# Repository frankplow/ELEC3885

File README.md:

# A robust and lightweight helmet-mounted safety camera for cycling
ELEC3885: Group Design Project, group 4 project at the University of Leeds.

The objective of this project is to design and produce a prototype for a camera to mount to the helmet of a cyclist, as well as a software suite for the analysis of footage and user documentation. The camera is intended as a safety device, for example for use in legal proceedings, rather than an 'action cam'. Because of this, it should be low-cost and should not require much effort by the user, for example charging, to use.

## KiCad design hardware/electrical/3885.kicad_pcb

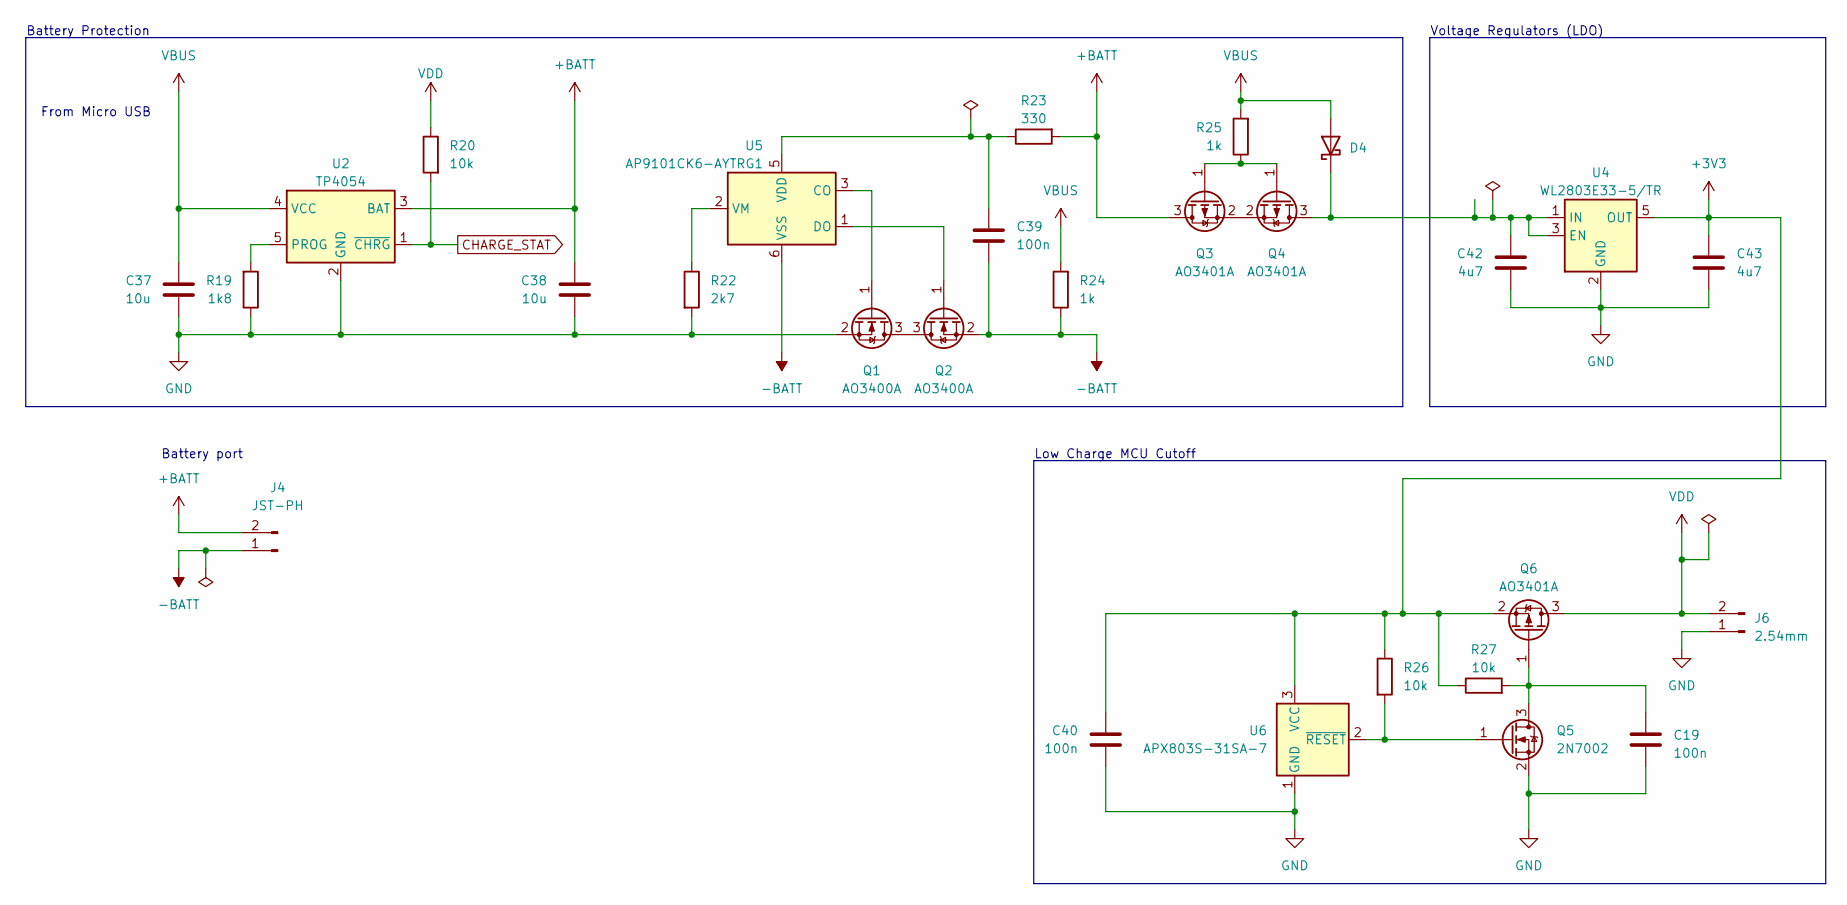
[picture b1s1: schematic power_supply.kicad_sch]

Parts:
C19, C39, C40: 100n; C_0402_1005Metric; Mfr. Part # CL05B104KO5NNNC; LCSC Part # C1525
C37, C38: 10u; C_0402_1005Metric; Mfr. Part # CL05A106MQ5NUNC; LCSC Part # C15525
C42, C43: 4u7; C_0402_1005Metric; Mfr. Part # CL05A475MP5NRNC; LCSC Part # C23733
D4: D_Schottky; D_SOD-323; Mfr. Part # 1N5819WS; LCSC Part # C191023
J4: JST-PH; JST_PH_S2B-PH-K_1x02_P2.00mm_Horizontal; Mfr. Part # S2B-PH-K-S(LF)(SN); LCSC Part # C173752
J6: 2.54mm; PinHeader_1x02_P2.54mm_Vertical
Q1, Q2: AO3400A; SOT-23; Mfr. Part # AO3400A; LCSC Part # C20917
Q3, Q4, Q6: AO3401A; SOT-23; Mfr. Part # AO3401A; LCSC Part # C15127
Q5: 2N7002; SOT-23; Mfr. Part # 2N7002; LCSC Part # C8545
R19: 1k8; R_0603_1608Metric; Mfr. Part # 0603WAF1801T5E; LCSC Part # C4177
R20, R26, R27: 10k; R_0402_1005Metric; Mfr. Part # 0402WGF1002TCE; LCSC Part # C25744
R22: 2k7; R_0603_1608Metric; Mfr. Part # 0603WAF2701T5E; LCSC Part # C13167
R23: 330; R_0402_1005Metric; Mfr. Part # 0402WGF3300TCE; LCSC Part # C25104
R24, R25: 1k; R_0402_1005Metric; Mfr. Part # 0402WGF1001TCE; LCSC Part # C11702
U2: TP4054; SOT-23-5; Mfr. Part # TP4054-42-SOT25R; LCSC Part # C32574
U4: WL2803E33-5/TR; SOT-23-5; Mfr. Part # WL2803E33-5/TR; LCSC Part # C192928
U5: AP9101CK6-AYTRG1; SOT-23-6; Mfr. Part # AP9101CK6-AYTRG1; LCSC Part # C507889
U6: APX803S-31SA-7; SOT-23; Mfr. Part # APX803S-31SA-7; LCSC Part # C129757

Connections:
+3V3: C40.1, C43.2, Q6.2 (S), R26.1, R27.1, U4.5 (OUT), U6.3 (VCC); also elsewhere on the board
+BATT: C38.2, J4.2, Q3.3 (D), R23.2, U2.3 (BAT)
-BATT: C39.1, J4.1, Q2.2 (S), R24.1, U5.6 (VSS)
CHARGE_STAT: R20.2, U2.1 (~CHRG); also elsewhere on the board
GND: C19.2, C37.2, C38.1, C40.2, C42.1, C43.1, J6.1, Q1.2 (S), Q5.2 (S), R19.1, R22.2, U2.2 (GND), U4.2 (GND), U6.1 (GND); also elsewhere on the board
unnamed: C42.2, D4.1 (K), Q4.3 (D), U4.1 (IN), U4.3 (EN)
unnamed: Q1.3 (D), Q2.3 (D)
unnamed: Q1.1 (G), U5.3 (CO)
unnamed: Q2.1 (G), U5.1 (DO)
unnamed: Q3.1 (G), Q4.1 (G), R25.1
unnamed: Q3.2 (S), Q4.2 (S)
unnamed: C19.1, Q5.3 (D), Q6.1 (G), R27.2
unnamed: Q5.1 (G), R26.2, U6.2 (~RESET)
unnamed: R19.2, U2.5 (PROG)
unnamed: C39.2, R23.1, U5.5 (VDD)
unnamed: R22.1, U5.2 (VM)
VBUS: C37.1, D4.2 (A), R24.2, R25.2, U2.4 (VCC); also elsewhere on the board
VDD: J6.2, Q6.3 (D), R20.1; also elsewhere on the board

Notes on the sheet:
Voltage Regulators (LDO)
Low Charge MCU Cutoff
From Micro USB
Battery Protection
Battery port

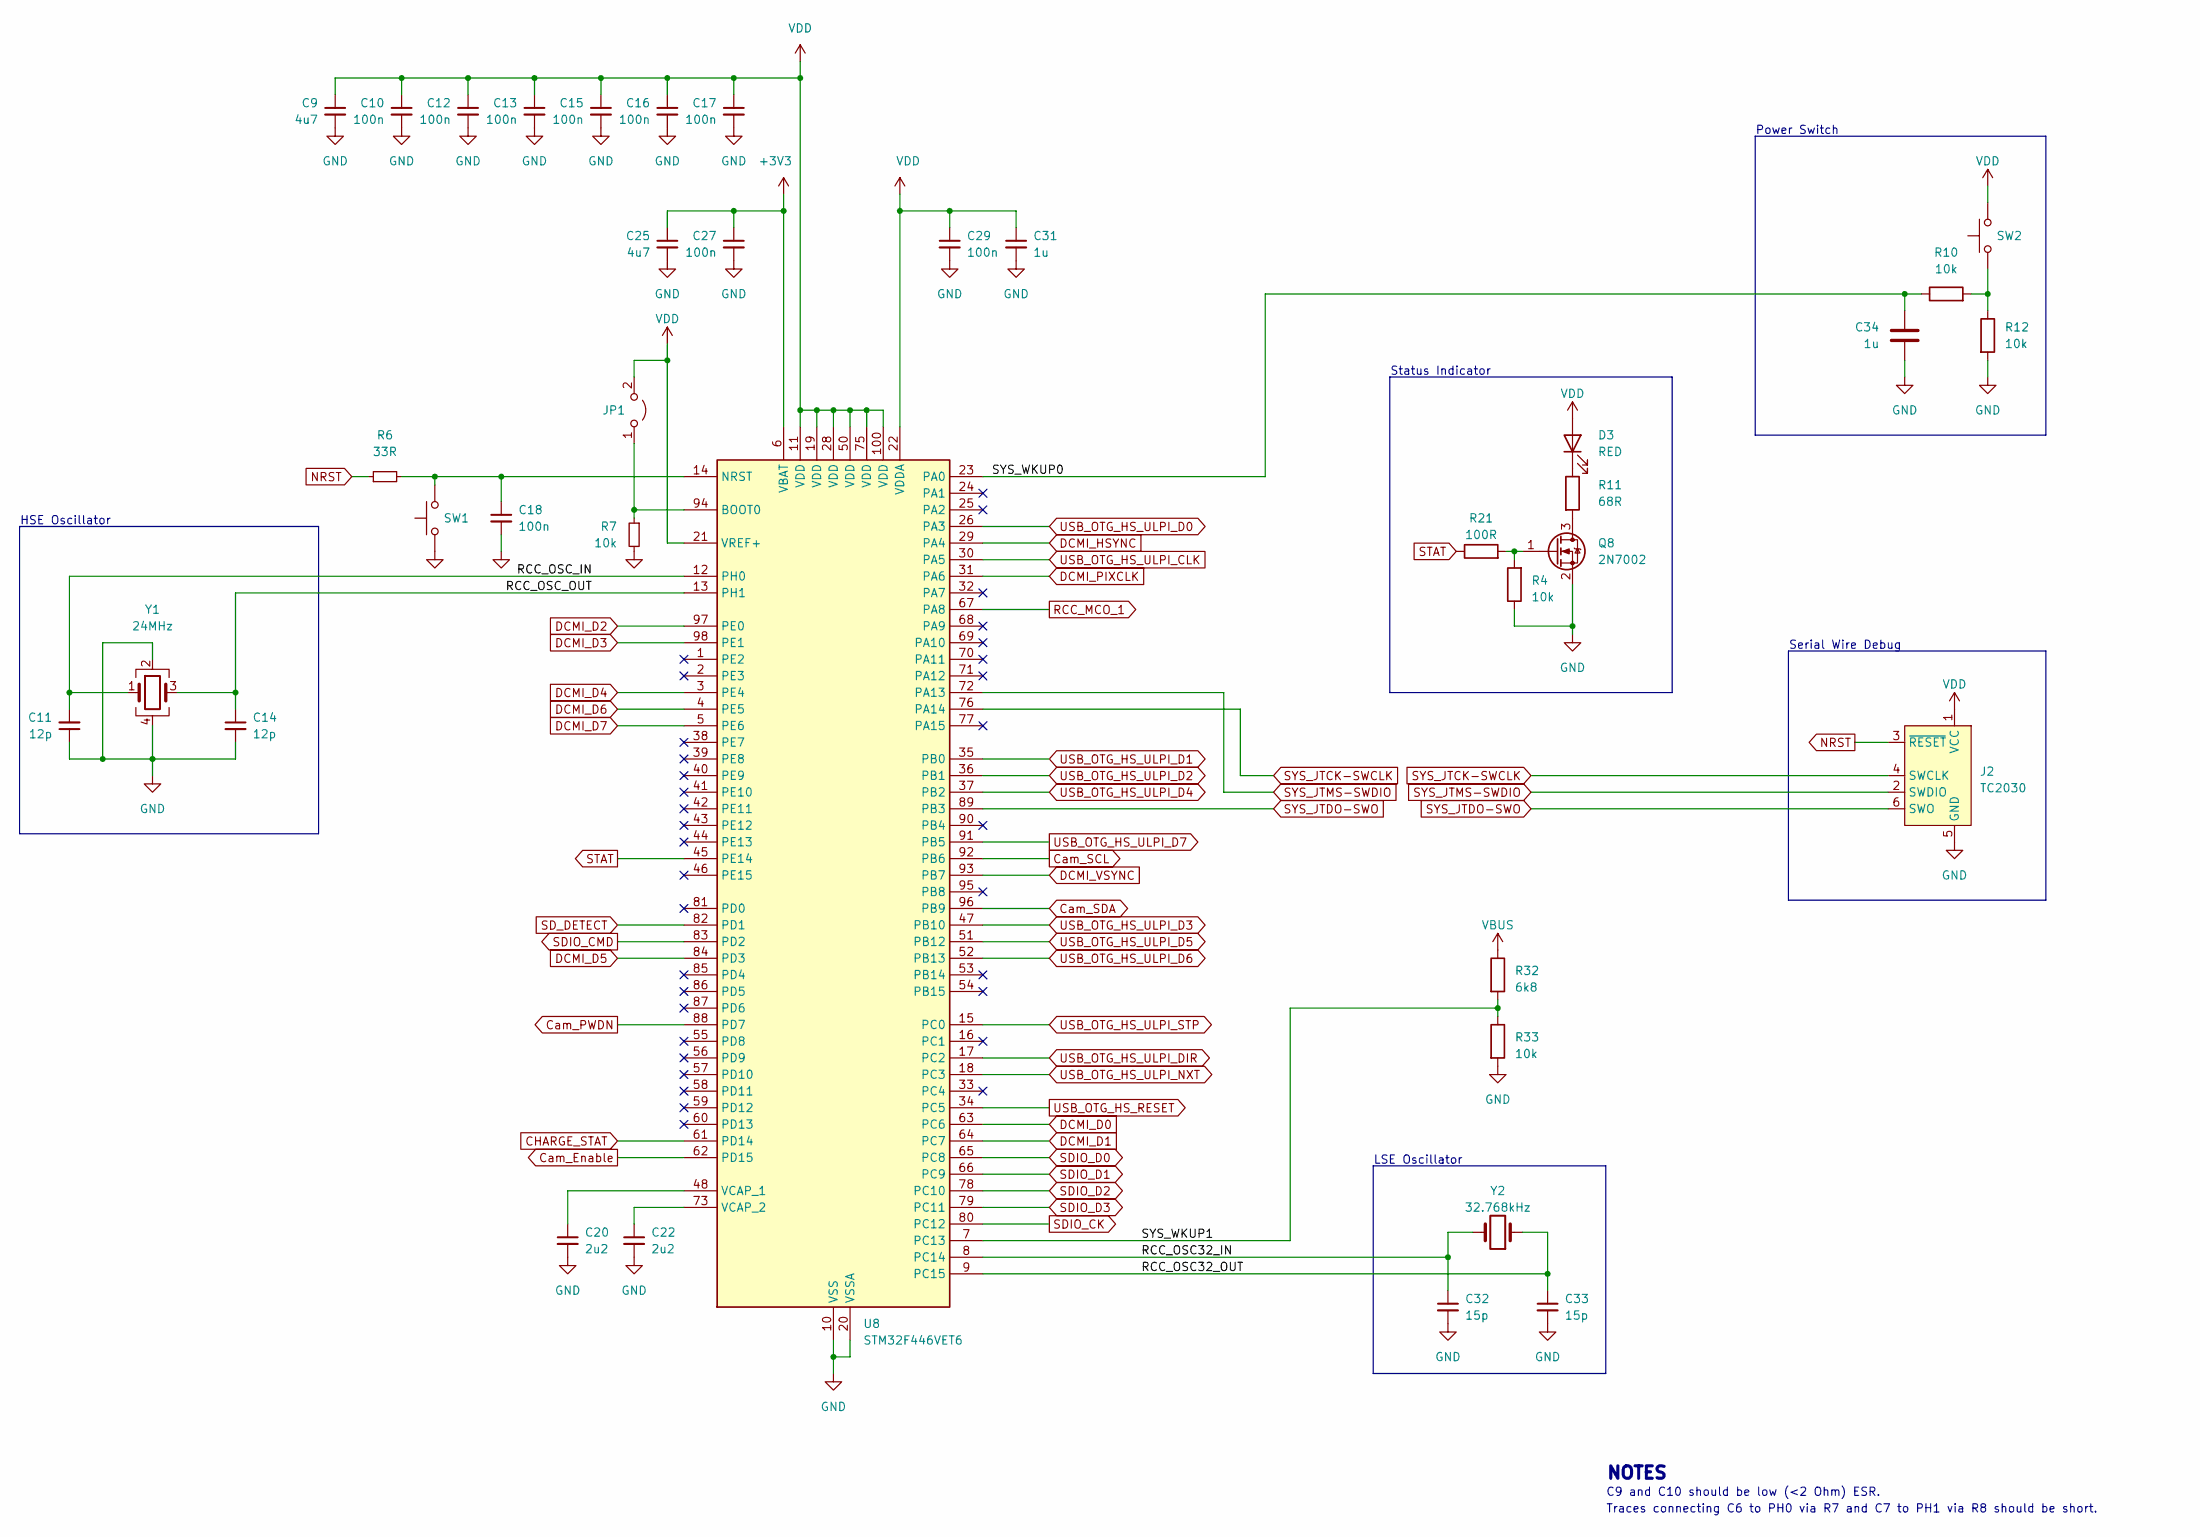
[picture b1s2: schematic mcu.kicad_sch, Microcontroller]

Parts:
C9, C25: 4u7; C_0402_1005Metric; Mfr. Part # CL05A475MP5NRNC; LCSC Part # C23733
C10, C12, C13, C15, C16, C17, C18, C27, C29: 100n; C_0402_1005Metric; Mfr. Part # CL05B104KO5NNNC; LCSC Part # C1525
C11, C14: 12p; C_0603_1608Metric; Mfr. Part # CL10C120JB8NNNC; LCSC Part # C38523
C20, C22: 2u2; C_0402_1005Metric; Mfr. Part # CL05A225MQ5NSNC; LCSC Part # C12530
C31, C34: 1u; C_0402_1005Metric; Mfr. Part # CL05A105KA5NQNC; LCSC Part # C52923
C32, C33: 15p; C_0603_1608Metric; Mfr. Part # CL10C150JB8NNNC; LCSC Part # C1644
D3: RED; Everlight_21-21S; Mfr. Part # 12-21SURC/S530-A3/TR8; LCSC Part # C131288
J2: TC2030; Tag-Connect_TC2030-IDC-FP_2x03_P1.27mm_Vertical
JP1: Jumper_2_Open; SolderJumper-2_P1.3mm_Open_Pad1.0x1.5mm
Q8: 2N7002; SOT-23; Mfr. Part # 2N7002; LCSC Part # C8545
R4: 10k; R_0402_1005Metric; Mfr. Part # 0402WGF1000TCE; LCSC Part # C25076
R6: 33R; R_0402_1005Metric; Mfr. Part # 0402WGF330JTCE; LCSC Part # C25105
R7, R10, R12, R33: 10k; R_0402_1005Metric; Mfr. Part # 0402WGF1002TCE; LCSC Part # C25744
R11: 68R; R_0603_1608Metric; Mfr. Part # 0603WAF680JT5E; LCSC Part # C27592
R21: 100R; R_0402_1005Metric; Mfr. Part # 0402WGF1000TCE; LCSC Part # C25076
R32: 6k8; R_0402_1005Metric; Mfr. Part # 0402WGF6801TCE; LCSC Part # C25917
SW1: TS-1187A-B-A-B; SW_SPST_XKB_TS-1187A; Mfr. Part # TS-1187A-B-A-B; LCSC Part # C318884
SW2: GT-TC018B-H0375-L1; G-Switch_GT-TC018; Mfr. Part # GT-TC018B-H0375-L1; LCSC Part # C2762970
U8: STM32F446VET6; LQFP-100_14x14mm_P0.5mm; Mfr. Part # STM32F446VET6; LCSC Part # C91929
Y1: 24MHz; Crystal_SMD_SeikoEpson_TSX3225-4Pin_3.2x2.5mm; Mfr. Part # X1E0000210129; LCSC Part # C255917
Y2: 32.768kHz; Crystal_SMD_3215-2Pin_3.2x1.5mm; Mfr. Part # Q13FC1350000400; LCSC Part # C32346

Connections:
+3V3: C25.1, C27.1, U8.6 (VBAT); also elsewhere on the board
/Microcontroller/RCC_OSC32_IN: C32.1, U8.8 (PC14), Y2.2
/Microcontroller/RCC_OSC32_OUT: C33.1, U8.9 (PC15), Y2.1
/Microcontroller/RCC_OSC_IN: C11.2, U8.12 (PH0), Y1.1
/Microcontroller/RCC_OSC_OUT: C14.1, U8.13 (PH1), Y1.3
/Microcontroller/SYS_WKUP0: C34.2, R10.1, U8.23 (PA0)
/Microcontroller/SYS_WKUP1: R32.2, R33.1, U8.7 (PC13)
CHARGE_STAT: U8.61 (PD14); also elsewhere on the board
Cam_Enable: U8.62 (PD15); also elsewhere on the board
Cam_PWDN: U8.88 (PD7); also elsewhere on the board
Cam_SCL: U8.92 (PB6); also elsewhere on the board
Cam_SDA: U8.96 (PB9); also elsewhere on the board
DCMI_D0: U8.63 (PC6); also elsewhere on the board
DCMI_D1: U8.64 (PC7); also elsewhere on the board
DCMI_D2: U8.97 (PE0); also elsewhere on the board
DCMI_D3: U8.98 (PE1); also elsewhere on the board
DCMI_D4: U8.3 (PE4); also elsewhere on the board
DCMI_D5: U8.84 (PD3); also elsewhere on the board
DCMI_D6: U8.4 (PE5); also elsewhere on the board
DCMI_D7: U8.5 (PE6); also elsewhere on the board
DCMI_HSYNC: U8.29 (PA4); also elsewhere on the board
DCMI_PIXCLK: U8.31 (PA6); also elsewhere on the board
DCMI_VSYNC: U8.93 (PB7); also elsewhere on the board
GND: C9.2, C10.2, C11.1, C12.2, C13.2, C14.2, C15.2, C16.2, C17.2, C18.2, C20.2, C22.2, C25.2, C27.2, C29.2, C31.2, C32.2, C33.2, C34.1, J2.5 (GND), Q8.2 (S), R4.1, R7.2, R12.2, R33.2, SW1.1, U8.10 (VSS), U8.20 (VSSA), U8.27 (VSS), U8.49 (VSS), U8.74 (VSS), U8.99 (VSS), Y1.2, Y1.4; also elsewhere on the board
NRST: J2.3 (~RESET), R6.1
unnamed: D3.1 (K), R11.1
unnamed: JP1.1 (A), R7.1, U8.94 (BOOT0)
unnamed: Q8.3 (D), R11.2
unnamed: Q8.1 (G), R4.2, R21.2
unnamed: R10.2, R12.1, SW2.1
unnamed: C18.1, R6.2, SW1.2, U8.14 (NRST)
unnamed: C20.1, U8.48 (VCAP_1)
unnamed: C22.1, U8.73 (VCAP_2)
RCC_MCO_1: U8.67 (PA8); also elsewhere on the board
SDIO_CK: U8.80 (PC12); also elsewhere on the board
SDIO_CMD: U8.83 (PD2); also elsewhere on the board
SDIO_D0: U8.65 (PC8); also elsewhere on the board
SDIO_D1: U8.66 (PC9); also elsewhere on the board
SDIO_D2: U8.78 (PC10); also elsewhere on the board
SDIO_D3: U8.79 (PC11); also elsewhere on the board
SD_DETECT: U8.82 (PD1); also elsewhere on the board
STAT: R21.1, U8.45 (PE14)
SYS_JTCK-SWCLK: J2.4 (SWCLK), U8.76 (PA14)
SYS_JTDO-SWO: J2.6 (SWO), U8.89 (PB3)
SYS_JTMS-SWDIO: J2.2 (SWDIO), U8.72 (PA13)
USB_OTG_HS_RESET: U8.34 (PC5); also elsewhere on the board
USB_OTG_HS_ULPI_CLK: U8.30 (PA5); also elsewhere on the board
USB_OTG_HS_ULPI_D0: U8.26 (PA3); also elsewhere on the board
USB_OTG_HS_ULPI_D1: U8.35 (PB0); also elsewhere on the board
USB_OTG_HS_ULPI_D2: U8.36 (PB1); also elsewhere on the board
USB_OTG_HS_ULPI_D3: U8.47 (PB10); also elsewhere on the board
USB_OTG_HS_ULPI_D4: U8.37 (PB2); also elsewhere on the board
USB_OTG_HS_ULPI_D5: U8.51 (PB12); also elsewhere on the board
USB_OTG_HS_ULPI_D6: U8.52 (PB13); also elsewhere on the board
USB_OTG_HS_ULPI_D7: U8.91 (PB5); also elsewhere on the board
USB_OTG_HS_ULPI_DIR: U8.17 (PC2); also elsewhere on the board
USB_OTG_HS_ULPI_NXT: U8.18 (PC3); also elsewhere on the board
USB_OTG_HS_ULPI_STP: U8.15 (PC0); also elsewhere on the board
VBUS: R32.1; also elsewhere on the board
VDD: C9.1, C10.1, C12.1, C13.1, C15.1, C16.1, C17.1, C29.1, C31.1, D3.2 (A), J2.1 (VCC), JP1.2 (B), SW2.2, U8.11 (VDD), U8.19 (VDD), U8.21 (VREF+), U8.22 (VDDA), U8.28 (VDD), U8.50 (VDD), U8.75 (VDD), U8.100 (VDD); also elsewhere on the board

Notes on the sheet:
C9 and C10 should be low (<2 Ohm) ESR.
Traces connecting C6 to PH0 via R7 and C7 to PH1 via R8 should be short.
LSE Oscillator
Serial Wire Debug
HSE Oscillator
Status Indicator
NOTES
Power Switch

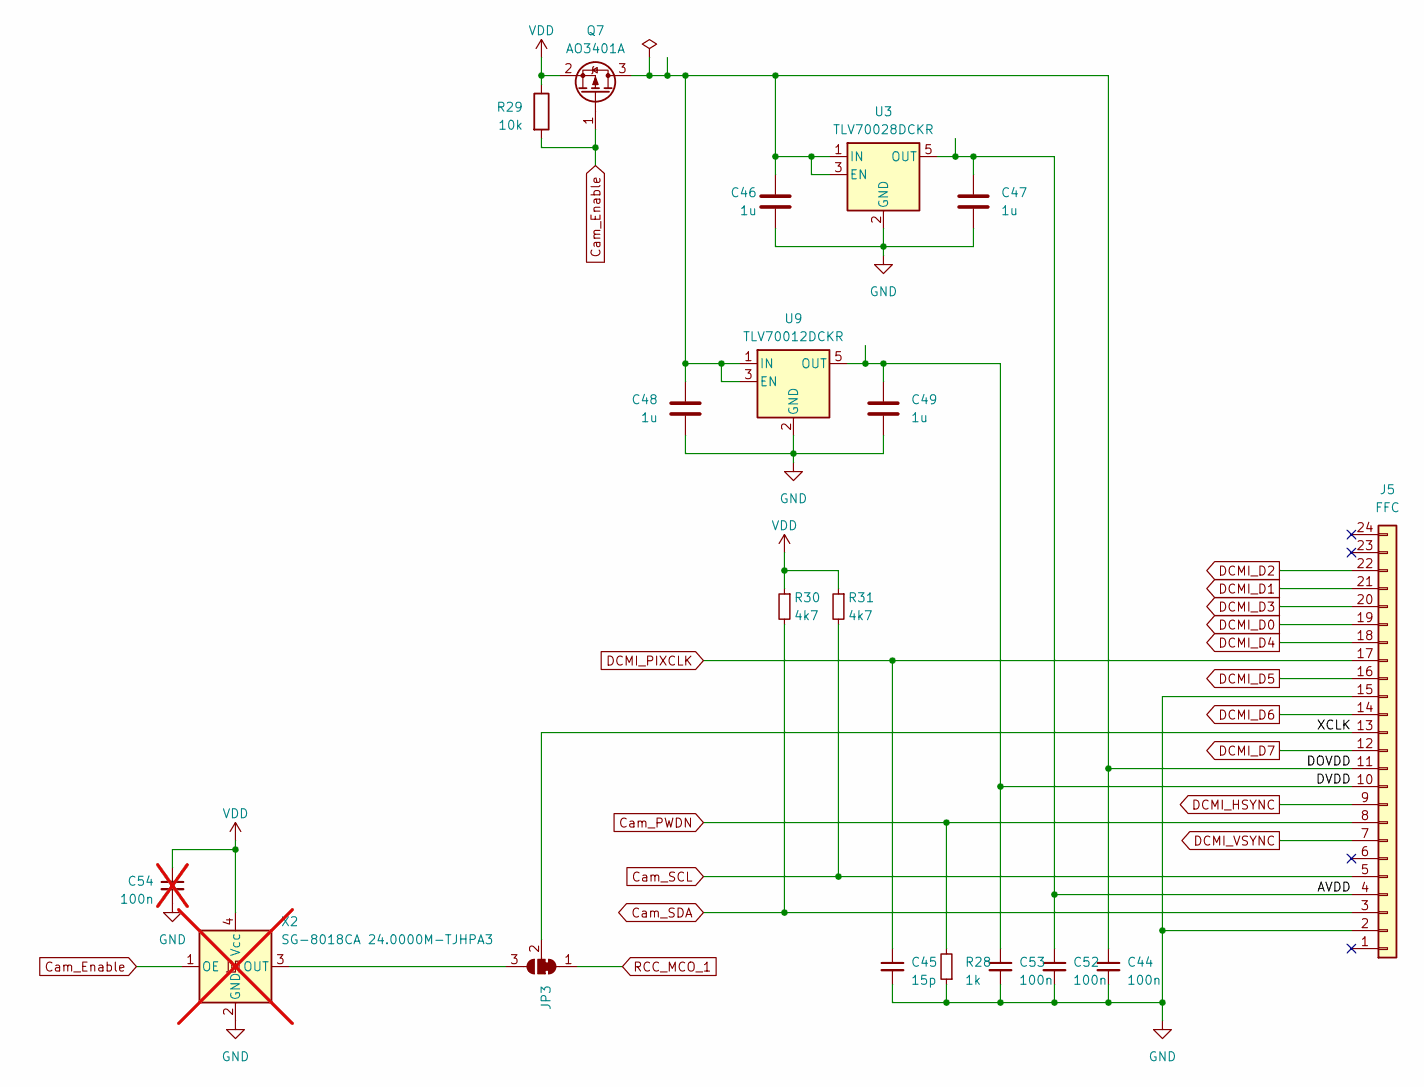
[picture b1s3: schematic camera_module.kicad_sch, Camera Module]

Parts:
C44, C52, C53: 100n; C_0402_1005Metric; Mfr. Part # CL05B104KO5NNNC; LCSC Part # C1525
C45: 15p; C_0603_1608Metric; Mfr. Part # CL10C150JB8NNNC; LCSC Part # C1644
C46, C47, C48, C49: 1u; C_0402_1005Metric; Mfr. Part # CL05A105KA5NQNC; LCSC Part # C52923
C54: 100n; C_0402_1005Metric; Mfr. Part # CL05B104KO5NNNC; LCSC Part # C1525; not fitted
J5: FFC; Jushuo_AFC07-S24ECA-00_1x24-1MP_P0.50_Horizontal; Mfr. Part # AFC07-S24ECA-00; LCSC Part # C262643
JP3: SolderJumper_3_Bridged12; SolderJumper-3_P1.3mm_Bridged12_Pad1.0x1.5mm
Q7: AO3401A; SOT-23; Mfr. Part # AO3401A; LCSC Part # C15127
R28: 1k; R_0402_1005Metric; Mfr. Part # 0402WGF1001TCE; LCSC Part # C11702
R29: 10k; R_0402_1005Metric; Mfr. Part # 0402WGF1002TCE; LCSC Part # C25744
R30, R31: 4k7; R_0402_1005Metric; Mfr. Part # 0402WGF4701TCE; LCSC Part # C25900
U3: TLV70028DCKR; SOT-353_SC-70-5; Mfr. Part # TLV70028DCKR; LCSC Part # C398921
U9: TLV70012DCKR; SOT-353_SC-70-5; Mfr. Part # TLV70012DCKR; LCSC Part # C96219
X2: SG-8018CA 24.0000M-TJHPA3; Oscillator_SMD_SeikoEpson_SG8002CA-4Pin_7.0x5.0mm_HandSolde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; not fitted

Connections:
/Camera Module/AVDD: C47.1, C52.1, J5.4, U3.5 (OUT)
/Camera Module/DOVDD: C44.1, C46.1, C48.1, J5.11, Q7.3 (D), U3.1 (IN), U3.3 (EN), U9.1 (IN), U9.3 (EN)
/Camera Module/DVDD: C49.1, C53.1, J5.10, U9.5 (OUT)
/Camera Module/XCLK: J5.13, JP3.2 (C)
Cam_Enable: Q7.1 (G), R29.2, X2.1 (OE); also elsewhere on the board
Cam_PWDN: J5.8, R28.2; also elsewhere on the board
Cam_SCL: J5.5, R31.2; also elsewhere on the board
Cam_SDA: J5.3, R30.2; also elsewhere on the board
DCMI_D0: J5.19; also elsewhere on the board
DCMI_D1: J5.21; also elsewhere on the board
DCMI_D2: J5.22; also elsewhere on the board
DCMI_D3: J5.20; also elsewhere on the board
DCMI_D4: J5.18; also elsewhere on the board
DCMI_D5: J5.16; also elsewhere on the board
DCMI_D6: J5.14; also elsewhere on the board
DCMI_D7: J5.12; also elsewhere on the board
DCMI_HSYNC: J5.9; also elsewhere on the board
DCMI_PIXCLK: C45.1, J5.17; also elsewhere on the board
DCMI_VSYNC: J5.7; also elsewhere on the board
GND: C44.2, C45.2, C46.2, C47.2, C48.2, C49.2, C52.2, C53.2, C54.2, J5.2, J5.15, R28.1, U3.2 (GND), U9.2 (GND), X2.2 (GND); also elsewhere on the board
unnamed: JP3.3 (B), X2.3 (OUT)
RCC_MCO_1: JP3.1 (A); also elsewhere on the board
VDD: C54.1, Q7.2 (S), R29.1, R30.1, R31.1, X2.4 (Vcc); also elsewhere on the board

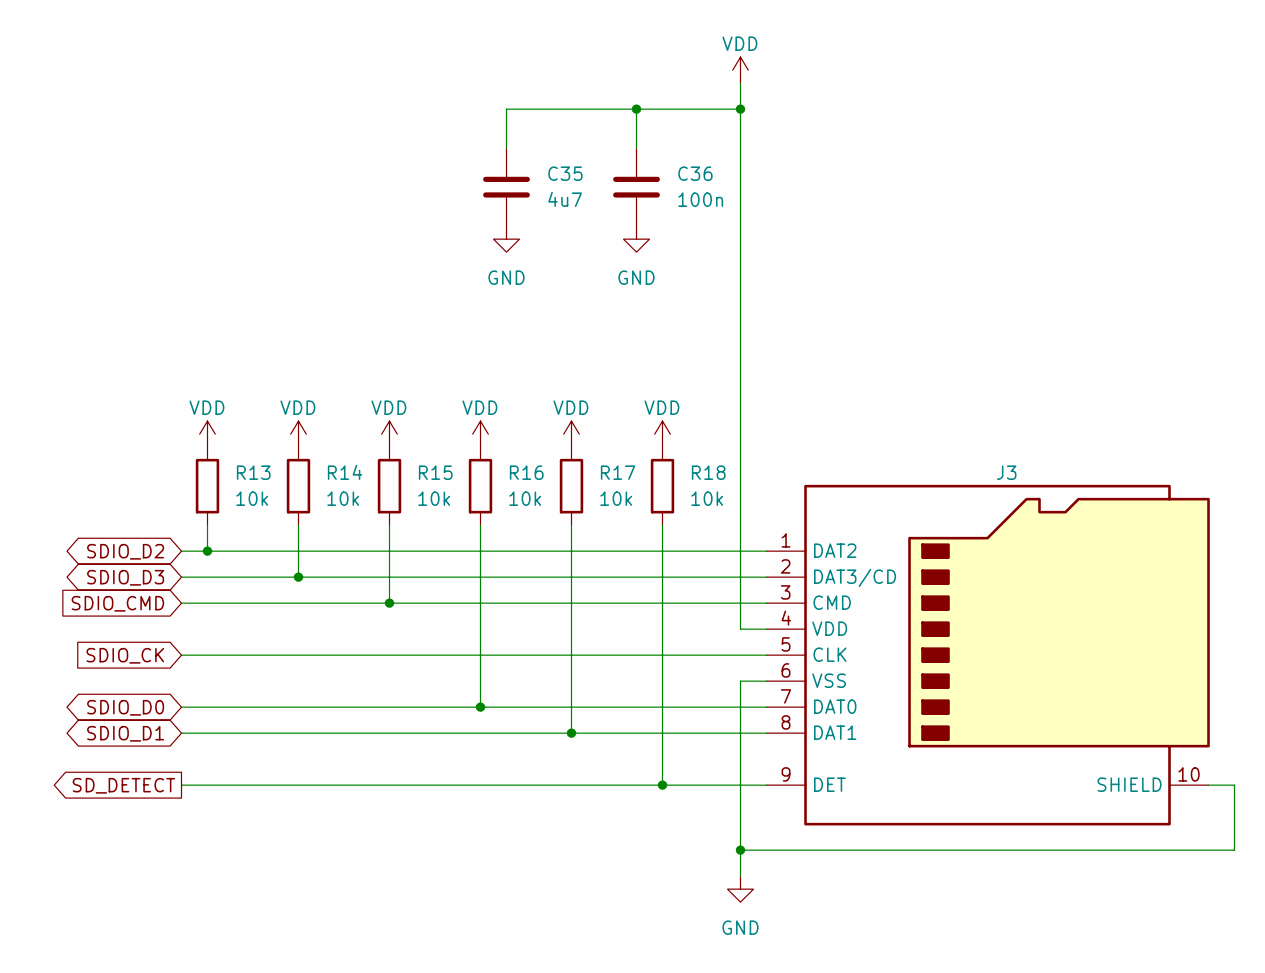
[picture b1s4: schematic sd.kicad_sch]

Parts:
C35: 4u7; C_0402_1005Metric; Mfr. Part # CL05A475MP5NRNC; LCSC Part # C23733
C36: 100n; C_0402_1005Metric; Mfr. Part # CL05B104KO5NNNC; LCSC Part # C1525
J3: Micro_SD_Card_Det1; microSD_HC_XKB_XKTF-N02-N; Mfr. Part # XKTF-N02-N; LCSC Part # C381084
R13, R14, R15, R16, R17, R18: 10k; R_0402_1005Metric; Mfr. Part # 0402WGF1002TCE; LCSC Part # C25744

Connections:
GND: C35.2, C36.2, J3.6 (VSS), J3.10 (SHIELD); also elsewhere on the board
SDIO_CK: J3.5 (CLK); also elsewhere on the board
SDIO_CMD: J3.3 (CMD), R15.2; also elsewhere on the board
SDIO_D0: J3.7 (DAT0), R16.2; also elsewhere on the board
SDIO_D1: J3.8 (DAT1), R17.2; also elsewhere on the board
SDIO_D2: J3.1 (DAT2), R13.2; also elsewhere on the board
SDIO_D3: J3.2 (DAT3/CD), R14.2; also elsewhere on the board
SD_DETECT: J3.9 (DET), R18.2; also elsewhere on the board
VDD: C35.1, C36.1, J3.4 (VDD), R13.1, R14.1, R15.1, R16.1, R17.1, R18.1; also elsewhere on the board

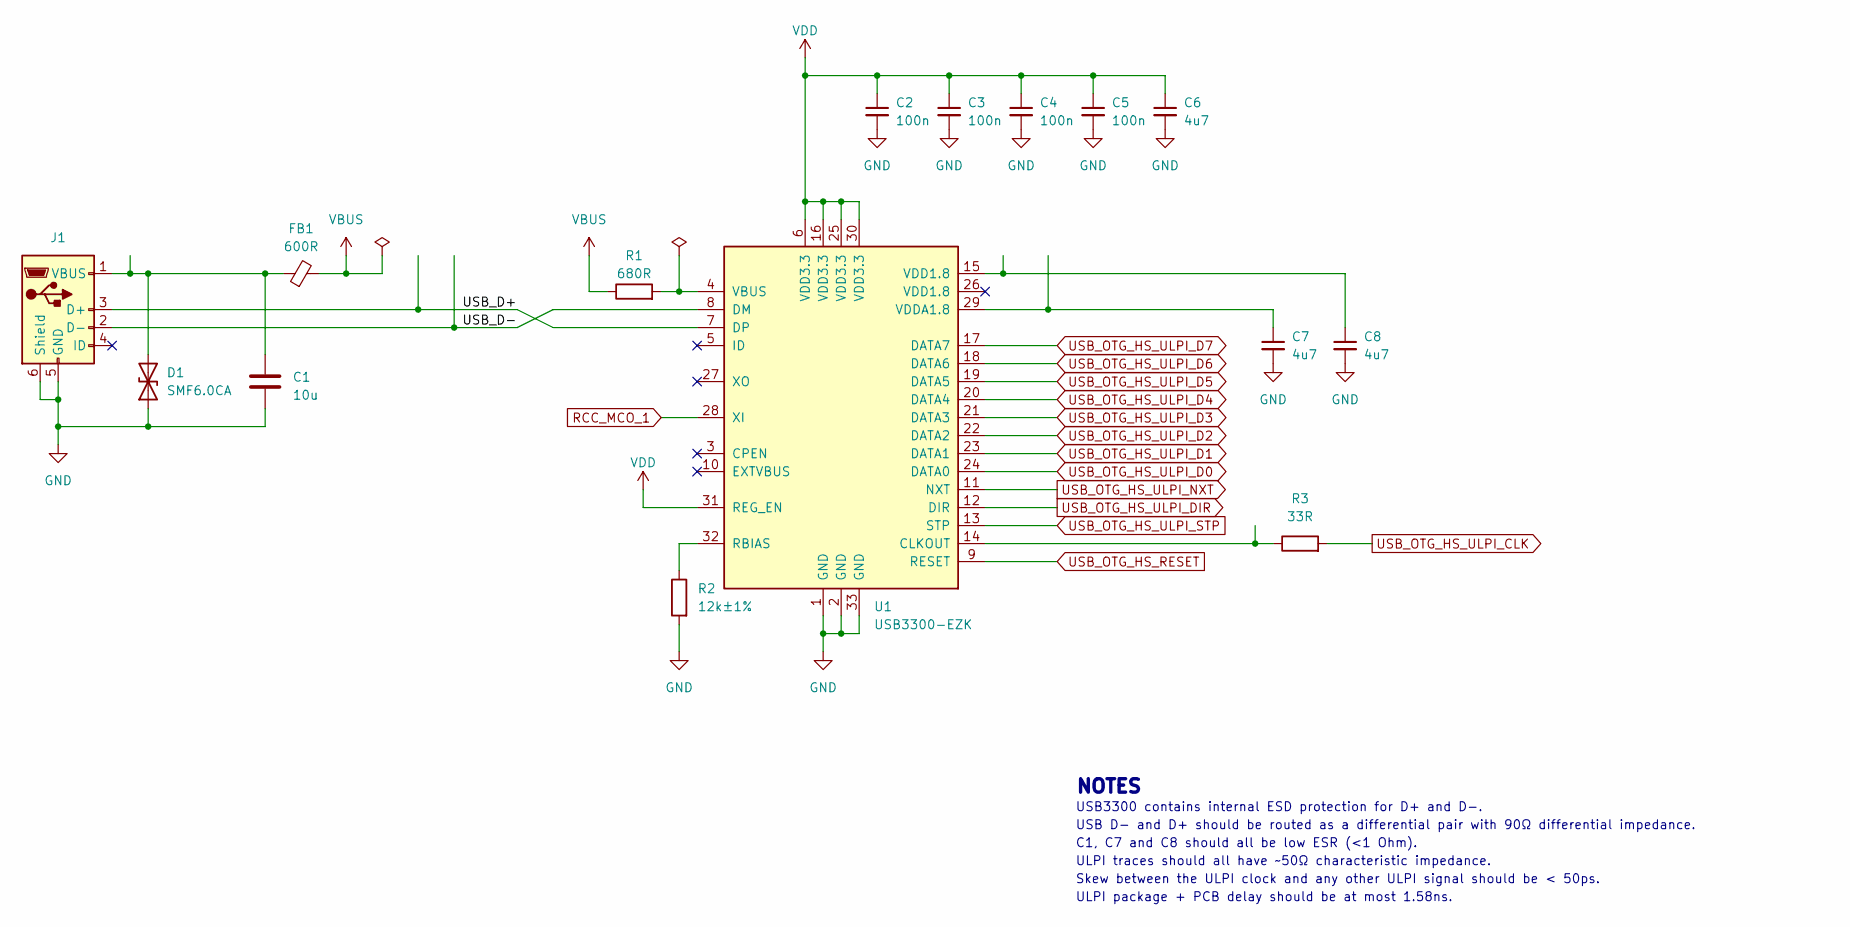
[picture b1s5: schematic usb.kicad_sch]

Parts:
C1: 10u; C_0402_1005Metric; Mfr. Part # CL05A106MQ5NUNC; LCSC Part # C15525
C2, C3, C4, C5: 100n; C_0402_1005Metric; Mfr. Part # CL05B104KO5NNNC; LCSC Part # C1525
C6, C7, C8: 4u7; C_0402_1005Metric; Mfr. Part # CL05A475MP5NRNC; LCSC Part # C23733
D1: SMF6.0CA; D_SOD-123F; Mfr. Part # SMF6.0CA; LCSC Part # C2990473
FB1: 600R; L_0805_2012Metric; Mfr. Part # GZ2012D601TF; LCSC Part # C1017
J1: USB_B_Micro; USB_Micro-B_Amphenol_10104110_Horizontal; Mfr. Part # 10104110-0001LF; LCSC Part # C2931352
R1: 680R; R_0402_1005Metric; Mfr. Part # 0402WGF6800TCE; LCSC Part # C25130
R2: 12k±1%; R_0402_1005Metric; Mfr. Part # 0402WGF1202TCE; LCSC Part # C25752
R3: 33R; R_0402_1005Metric; Mfr. Part # 0402WGF330JTCE; LCSC Part # C25105
U1: USB3300-EZK; QFN-32-1EP_5x5mm_P0.5mm_EP3.45x3.45mm; Mfr. Part # USB3300-EZK-TR; LCSC Part # C108383

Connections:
/USB/USB_D+: J1.3 (D+), U1.7 (DP)
/USB/USB_D-: J1.2 (D-), U1.8 (DM)
GND: C1.2, C2.2, C3.2, C4.2, C5.2, C6.2, C7.2, C8.2, D1.1 (A1), J1.5 (GND), J1.6 (Shield), R2.2, U1.1 (GND), U1.2 (GND), U1.33 (GND); also elsewhere on the board
unnamed: C8.1, U1.15 (VDD1.8)
unnamed: C1.1, D1.2 (A2), FB1.1, J1.1 (VBUS)
unnamed: R3.1, U1.14 (CLKOUT)
unnamed: R2.1, U1.32 (RBIAS)
unnamed: R1.2, U1.4 (VBUS)
unnamed: C7.1, U1.29 (VDDA1.8)
RCC_MCO_1: U1.28 (XI); also elsewhere on the board
USB_OTG_HS_RESET: U1.9 (RESET); also elsewhere on the board
USB_OTG_HS_ULPI_CLK: R3.2; also elsewhere on the board
USB_OTG_HS_ULPI_D0: U1.24 (DATA0); also elsewhere on the board
USB_OTG_HS_ULPI_D1: U1.23 (DATA1); also elsewhere on the board
USB_OTG_HS_ULPI_D2: U1.22 (DATA2); also elsewhere on the board
USB_OTG_HS_ULPI_D3: U1.21 (DATA3); also elsewhere on the board
USB_OTG_HS_ULPI_D4: U1.20 (DATA4); also elsewhere on the board
USB_OTG_HS_ULPI_D5: U1.19 (DATA5); also elsewhere on the board
USB_OTG_HS_ULPI_D6: U1.18 (DATA6); also elsewhere on the board
USB_OTG_HS_ULPI_D7: U1.17 (DATA7); also elsewhere on the board
USB_OTG_HS_ULPI_DIR: U1.12 (DIR); also elsewhere on the board
USB_OTG_HS_ULPI_NXT: U1.11 (NXT); also elsewhere on the board
USB_OTG_HS_ULPI_STP: U1.13 (STP); also elsewhere on the board
VBUS: FB1.2, R1.1; also elsewhere on the board
VDD: C2.1, C3.1, C4.1, C5.1, C6.1, U1.6 (VDD3.3), U1.16 (VDD3.3), U1.25 (VDD3.3), U1.30 (VDD3.3), U1.31 (REG_EN); also elsewhere on the board

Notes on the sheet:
USB D- and D+ should be routed as a differential pair with 90Ω differential impedance.
ULPI package + PCB delay should be at most 1.58ns.
NOTES
USB3300 contains internal ESD protection for D+ and D-.
C1, C7 and C8 should all be low ESR (<1 Ohm).
Skew between the ULPI clock and any other ULPI signal should be < 50ps.
ULPI traces should all have ~50Ω characteristic impedance.

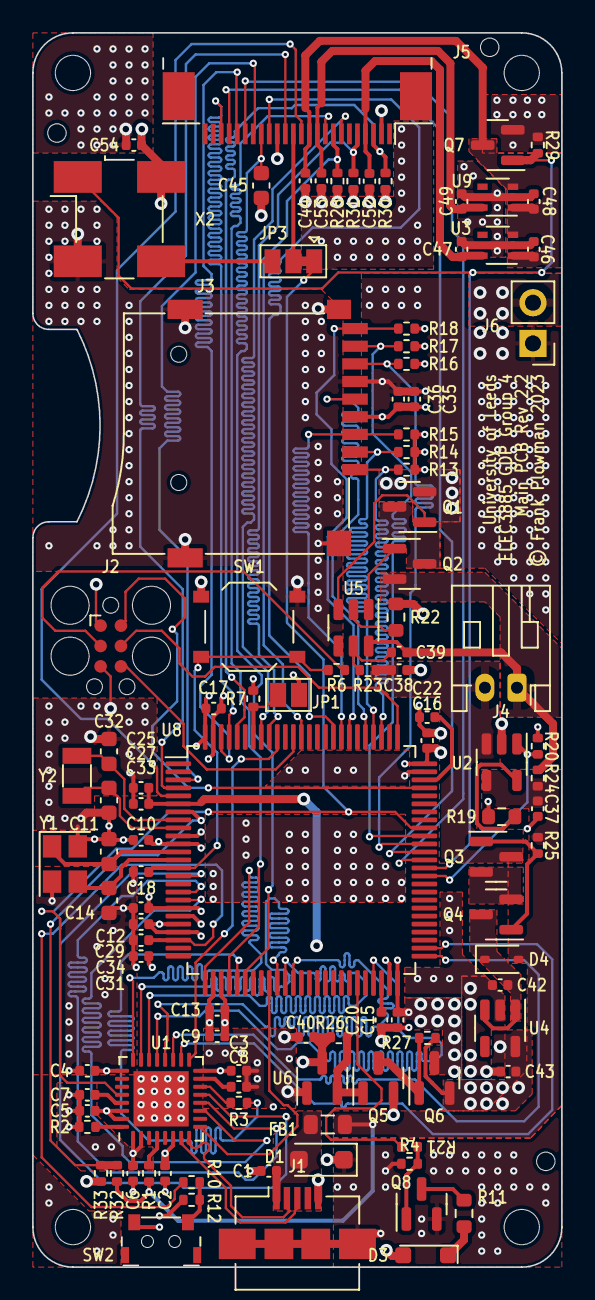
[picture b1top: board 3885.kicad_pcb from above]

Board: 4 copper layers, 33.0 x 77.0 mm, 107 parts (0 on the bottom side), 86 nets.

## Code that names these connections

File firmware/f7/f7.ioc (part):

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Mcu.Name=STM32F746NGHx
Mcu.Package=TFBGA216
Mcu.UserName=STM32F746NGHx
PA0/WKUP.GPIOParameters=GPIO_PuPd,GPIO_Label,GPIO_Mode
PA0/WKUP.GPIO_Label=ARDUINO A0
PA0/WKUP.GPIO_Mode=GPIO_MODE_ANALOG
PA0/WKUP.GPIO_PuPd=GPIO_NOPULL
PA0/WKUP.Signal=ADCx_IN0
PA1.GPIOParameters=GPIO_Label
PA1.GPIO_Label=RMII_REF_CLK [LAN8742A-CZ-TR_REFCLK0]
PA1.Signal=ETH_REF_CLK
PA10.GPIOParameters=GPIO_Label
PA10.GPIO_Label=OTG_FS_ID
PA10.Signal=USB_OTG_FS_ID
PA11.GPIOParameters=GPIO_Label
PA11.GPIO_Label=OTG_FS_N
PA11.Signal=USB_OTG_FS_DM
PA12.GPIOParameters=GPIO_Label
PA12.GPIO_Label=OTG_FS_P
PA12.Signal=USB_OTG_FS_DP
PA13.GPIOParameters=GPIO_Label
PA13.GPIO_Label=SWDIO
PA13.Mode=Trace_Asynchronous_SW
PA13.Signal=SYS_JTMS-SWDIO
PA14.GPIOParameters=GPIO_Label
PA14.GPIO_Label=SWCLK
PA14.Mode=Trace_Asynchronous_SW
PA14.Signal=SYS_JTCK-SWCLK
PA15.GPIOParameters=GPIO_ModeDefaultPP,GPIO_Speed,GPIO_PuPd,GPIO_Label
PA15.GPIO_Label=ARDUINO PWM/D9
PA15.GPIO_ModeDefaultPP=GPIO_MODE_AF_PP
PA15.GPIO_PuPd=GPIO_NOPULL
PA15.GPIO_Speed=GPIO_SPEED_FREQ_LOW
PA15.Signal=S_TIM2_CH1_ETR
PA2.GPIOParameters=GPIO_Label
PA2.GPIO_Label=RMII_MDIO [LAN8742A-CZ-TR_MDIO]
PA2.Signal=ETH_MDIO
PA3.GPIOParameters=GPIO_Label
PA3.GPIO_Label=ULPI_D0 [USB3320C-EZK_D0]
PA3.Mode=Device_HS
PA3.Signal=USB_OTG_HS_ULPI_D0
PA4.GPIOParameters=GPIO_Label
PA4.GPIO_Label=DCMI_HSYNC
PA4.Mode=Slave_8_bits_External_Synchro
PA4.Signal=DCMI_HSYNC
PA5.GPIOParameters=GPIO_Label
PA5.GPIO_Label=ULPI_CLK [USB3320C-EZK_CLKOUT]
PA5.Mode=Device_HS
PA5.Signal=USB_OTG_HS_ULPI_CK
PA6.Mode=Slave_8_bits_External_Synchro
PA6.Signal=DCMI_PIXCLK
PA7.GPIOParameters=GPIO_Label
PA7.GPIO_Label=RMII_CRS_DV [LAN8742A-CZ-TR_CRS_DV]
PA7.Signal=ETH_CRS_DV
PA8.GPIOParameters=GPIO_ModeDefaultPP,GPIO_Speed,GPIO_PuPd,GPIO_Label
PA8.GPIO_Label=ARDUINO PWM/D10
PA8.GPIO_ModeDefaultPP=GPIO_MODE_AF_PP
PA8.GPIO_PuPd=GPIO_NOPULL
PA8.GPIO_Speed=GPIO_SPEED_FREQ_LOW
PA8.Signal=S_TIM1_CH1
PA9.GPIOParameters=GPIO_Speed,GPIO_PuPd,GPIO_Label,GPIO_Mode
PA9.GPIO_Label=VCP_TX [STM32F103CBT6_PA3]
PA9.GPIO_Mode=GPIO_MODE_AF_PP
PA9.GPIO_PuPd=GPIO_NOPULL
PA9.GPIO_Speed=GPIO_SPEED_FREQ_LOW
PA9.Signal=USART1_TX
PB0.GPIOParameters=GPIO_Label
PB0.GPIO_Label=ULPI_D1 [USB3320C-EZK_D1]
PB0.Mode=Device_HS
PB0.Signal=USB_OTG_HS_ULPI_D1
PB1.GPIOParameters=GPIO_Label
PB1.GPIO_Label=ULPI_D2 [USB3320C-EZK_D2]
PB1.Mode=Device_HS
PB1.Signal=USB_OTG_HS_ULPI_D2
PB10.GPIOParameters=GPIO_Label
PB10.GPIO_Label=ULPI_D3 [USB3320C-EZK_D3]
PB10.Mode=Device_HS
PB10.Signal=USB_OTG_HS_ULPI_D3
PB11.GPIOParameters=GPIO_Label
PB11.GPIO_Label=ULPI_D4 [USB3320C-EZK_D4]
PB11.Mode=Device_HS
PB11.Signal=USB_OTG_HS_ULPI_D4
PB12.GPIOParameters=GPIO_Label
PB12.GPIO_Label=ULPI_D5 [USB3320C-EZK_D5]
PB12.Mode=Device_HS
PB12.Signal=USB_OTG_HS_ULPI_D5
PB13.GPIOParameters=GPIO_Label
PB13.GPIO_Label=ULPI_D6 [USB3320C-EZK_D6]
PB13.Mode=Device_HS
PB13.Signal=USB_OTG_HS_ULPI_D6
PB14.GPIOParameters=GPIO_Speed,GPIO_PuPd,GPIO_Label,GPIO_Mode
PB14.GPIO_Label=ARDUINO MISO/D12
PB14.GPIO_Mode=GPIO_MODE_AF_PP
PB14.GPIO_PuPd=GPIO_NOPULL
PB14.GPIO_Speed=GPIO_SPEED_FREQ_LOW
PB14.Signal=SPI2_MISO
PB15.GPIOParameters=GPIO_Speed,GPIO_PuPd,GPIO_Label,GPIO_Mode
PB15.GPIO_Label=ARDUINO MOSI/PWM/D11
PB15.GPIO_Mode=GPIO_MODE_AF_PP
PB15.GPIO_PuPd=GPIO_NOPULL
PB15.GPIO_Speed=GPIO_SPEED_FREQ_LOW
PB15.Signal=SPI2_MOSI
PB2.Signal=QUADSPI_CLK
PB3.GPIOParameters=GPIO_Label
PB3.GPIO_Label=SWO
PB3.Mode=Trace_Asynchronous_SW
PB3.Signal=SYS_JTDO-SWO
PB4.GPIOParameters=GPIO_ModeDefaultPP,GPIO_Speed,GPIO_PuPd,GPIO_Label
PB4.GPIO_Label=ARDUINO PWM/D3
PB4.GPIO_ModeDefaultPP=GPIO_MODE_AF_PP
PB4.GPIO_PuPd=GPIO_NOPULL
PB4.GPIO_Speed=GPIO_SPEED_FREQ_LOW
PB4.Signal=S_TIM3_CH1
PB5.GPIOParameters=GPIO_Label
PB5.GPIO_Label=ULPI_D7 [USB3320C-EZK_D7]
PB5.Mode=Device_HS
PB5.Signal=USB_OTG_HS_ULPI_D7
PB6.GPIOParameters=GPIO_Label
PB6.GPIO_Label=QSPI_NCS [N25Q128A13EF840E_S]
PB6.Signal=QUADSPI_BK1_NCS
PB7.GPIOParameters=GPIO_Speed,GPIO_PuPd,GPIO_Label,GPIO_Mode
PB7.GPIO_Label=VCP_RX [STM32F103CBT6_PA2]
PB7.GPIO_Mode=GPIO_MODE_AF_PP
PB7.GPIO_PuPd=GPIO_NOPULL
PB7.GPIO_Speed=GPIO_SPEED_FREQ_LOW
PB7.Signal=USART1_RX
PB8.GPIOParameters=GPIO_Speed,GPIO_PuPd,GPIO_Label,GPIO_Mode
PB8.GPIO_Label=ARDUINO SCL/D15
PB8.GPIO_Mode=GPIO_MODE_AF_OD
PB8.GPIO_PuPd=GPIO_NOPULL
PB8.GPIO_Speed=GPIO_SPEED_FREQ_LOW
PB8.Mode=I2C
PB8.Signal=I2C1_SCL
PB9.GPIOParameters=GPIO_Speed,GPIO_PuPd,GPIO_Label,GPIO_Mode
PB9.GPIO_Label=ARDUINO SDA/D14
PB9.GPIO_Mode=GPIO_MODE_AF_OD
PB9.GPIO_PuPd=GPIO_NOPULL
PB9.GPIO_Speed=GPIO_SPEED_FREQ_LOW
PB9.Mode=I2C
PB9.Signal=I2C1_SDA
PC0.GPIOParameters=GPIO_Label
PC0.GPIO_Label=ULPI_STP [USB3320C-EZK_STP]
PC0.Mode=Device_HS
PC0.Signal=USB_OTG_HS_ULPI_STP
PC1.GPIOParameters=GPIO_Label
PC1.GPIO_Label=RMII_MDC [LAN8742A-CZ-TR_MDC]
PC1.Signal=ETH_MDC
PC10.GPIOParameters=GPIO_Label
PC10.GPIO_Label=SDMMC_D2
PC10.Mode=SD_4_bits_Wide_bus
PC10.Signal=SDMMC1_D2
PC11.GPIOParameters=GPIO_Label
PC11.GPIO_Label=SDMMC_D3
PC11.Mode=SD_4_bits_Wide_bus
PC11.Signal=SDMMC1_D3
PC12.GPIOParameters=GPIO_Label
PC12.GPIO_Label=SDMMC_CK
PC12.Mode=SD_4_bits_Wide_bus
PC12.Signal=SDMMC1_CK
PC13.GPIOParameters=GPIO_Label
PC13.GPIO_Label=uSD_Detect
PC13.Signal=GPIO_Input
PC14/OSC32_IN.GPIOParameters=GPIO_Label
PC14/OSC32_IN.GPIO_Label=RCC_OSC32_IN
PC14/OSC32_IN.Signal=RCC_OSC32_IN
PC15/OSC32_OUT.GPIOParameters=GPIO_Label
PC15/OSC32_OUT.GPIO_Label=RCC_OSC32_OUT
PC15/OSC32_OUT.Signal=RCC_OSC32_OUT
PC2.GPIOParameters=GPIO_Label
PC2.GPIO_Label=ULPI_DIR [USB3320C-EZK_DIR]
PC2.Mode=Device_HS
PC2.Signal=USB_OTG_HS_ULPI_DIR
PC3.GPIOParameters=GPIO_Label
PC3.GPIO_Label=FMC_SDCKE0 [MT48LC4M32B2B5-6A_CKE]
PC3.Signal=FMC_SDCKE0
PC4.GPIOParameters=GPIO_Label
PC4.GPIO_Label=RMII_RXD0 [LAN8742A-CZ-TR_RXD0]
PC4.Signal=ETH_RXD0
PC5.GPIOParameters=GPIO_Label
PC5.GPIO_Label=RMII_RXD1 [LAN8742A-CZ-TR_RXD1]
PC5.Signal=ETH_RXD1
PC6.GPIOParameters=GPIO_Label
PC6.GPIO_Label=ARDUINO TX/D1
PC6.Signal=USART6_TX
PC7.GPIOParameters=GPIO_Label
PC7.GPIO_Label=ARDUINO RX/D0
PC7.Signal=USART6_RX
PC8.Mode=SD_4_bits_Wide_bus
PC8.Signal=SDMMC1_D0
PC9.Mode=SD_4_bits_Wide_bus
PC9.Signal=SDMMC1_D1
PD0.GPIOParameters=GPIO_Label
PD0.GPIO_Label=FMC_D2 [MT48LC4M32B2B5-6A_DQ2]
PD0.Signal=FMC_D2_DA2
PD1.GPIOParameters=GPIO_Label
PD1.GPIO_Label=FMC_D3 [MT48LC4M32B2B5-6A_DQ3]
PD1.Signal=FMC_D3_DA3
PD10.GPIOParameters=GPIO_Label
PD10.GPIO_Label=FMC_D15 [MT48LC4M32B2B5-6A_DQ15]
PD10.Signal=FMC_D15_DA15
PD11.GPIOParameters=GPIO_Label
PD11.GPIO_Label=QSPI_D0 [N25Q128A13EF840E_DQ0]
PD11.Signal=QUADSPI_BK1_IO0
PD12.GPIOParameters=GPIO_Label
PD12.GPIO_Label=QSPI_D1 [N25Q128A13EF840E_DQ1]
PD12.Signal=QUADSPI_BK1_IO1
PD13.GPIOParameters=GPIO_Label
PD13.GPIO_Label=QSPI_D3 [N25Q128A13EF840E_DQ3]
PD13.Signal=QUADSPI_BK1_IO3
PD14.GPIOParameters=GPIO_Label
PD14.GPIO_Label=FMC_D0 [MT48LC4M32B2B5-6A_DQ0]
PD14.Signal=FMC_D0_DA0
PD15.GPIOParameters=GPIO_Label
PD15.GPIO_Label=FMC_D1 [MT48LC4M32B2B5-6A_DQ1]
PD15.Signal=FMC_D1_DA1
PD2.GPIOParameters=GPIO_Label
PD2.GPIO_Label=SDMMC_D0
PD2.Mode=SD_4_bits_Wide_bus
PD2.Signal=SDMMC1_CMD
PD3.GPIOParameters=GPIO_Label
PD3.GPIO_Label=DCMI_D5
PD3.Mode=Slave_8_bits_External_Synchro
PD3.Signal=DCMI_D5
PD4.GPIOParameters=GPIO_Label
PD4.GPIO_Label=OTG_FS_OverCurrent [STMPS2141STR_Fault]
PD4.Signal=GPIO_Input
PD5.GPIOParameters=PinState,GPIO_Label
PD5.GPIO_Label=OTG_FS_PowerSwitchOn [STMPS2141STR_EN]
PD5.PinState=GPIO_PIN_SET
PD5.Signal=GPIO_Output
PD6.GPIOParameters=GPIO_Label,GPIO_ModeDefaultEXTI
PD6.GPIO_Label=Audio_INT
PD6.GPIO_ModeDefaultEXTI=GPIO_MODE_EVT_RISING
PD6.Signal=GPXTI6
PD7.GPIOParameters=GPIO_Label
PD7.GPIO_Label=SPDIF_RX0 [74LVC1G04SE_4]
PD7.Signal=SPDIFRX_IN0
PD8.GPIOParameters=GPIO_Label
PD8.GPIO_Label=FMC_D13 [MT48LC4M32B2B5-6A_DQ13]
PD8.Signal=FMC_D13_DA13
PD9.GPIOParameters=GPIO_Label
PD9.GPIO_Label=FMC_D14 [MT48LC4M32B2B5-6A_DQ14]
PD9.Signal=FMC_D14_DA14
PE0.GPIOParameters=GPIO_Label
PE0.GPIO_Label=FMC_NBL0 [MT48LC4M32B2B5-6A_DQM0]
PE0.Signal=FMC_NBL0
PE1.GPIOParameters=GPIO_Label
PE1.GPIO_Label=FMC_NBL1 [MT48LC4M32B2B5-6A_DQM1]
PE1.Signal=FMC_NBL1
PE10.GPIOParameters=GPIO_Label
PE10.GPIO_Label=FMC_D7 [MT48LC4M32B2B5-6A_DQ7]
PE10.Signal=FMC_D7_DA7
PE11.GPIOParameters=GPIO_Label
PE11.GPIO_Label=FMC_D8 [MT48LC4M32B2B5-6A_DQ8]
PE11.Signal=FMC_D8_DA8
PE12.GPIOParameters=GPIO_Label
PE12.GPIO_Label=FMC_D9 [MT48LC4M32B2B5-6A_DQ9]
PE12.Signal=FMC_D9_DA9
PE13.GPIOParameters=GPIO_Label
PE13.GPIO_Label=FMC_D10 [MT48LC4M32B2B5-6A_DQ10]
PE13.Signal=FMC_D10_DA10
PE14.GPIOParameters=GPIO_Label
PE14.GPIO_Label=FMC_D11 [MT48LC4M32B2B5-6A_DQ11]
PE14.Signal=FMC_D11_DA11
PE15.GPIOParameters=GPIO_Label
PE15.GPIO_Label=FMC_D12 [MT48LC4M32B2B5-6A_DQ12]
PE15.Signal=FMC_D12_DA12
PE2.GPIOParameters=GPIO_Label
PE2.GPIO_Label=QSPI_D2 [N25Q128A13EF840E_DQ2]
PE2.Signal=QUADSPI_BK1_IO2
PE3.GPIOParameters=GPIO_Label
PE3.GPIO_Label=OTG_HS_OverCurrent [STMPS2151STR_FAULT]
PE3.Signal=GPIO_Input
PE4.GPIOParameters=GPIO_Label
PE4.GPIO_Label=LCD_B0 [RK043FN48H-CT672B_B0]
PE4.Signal=LTDC_B0
PE5.GPIOParameters=GPIO_Label
PE5.GPIO_Label=DCMI_D6
PE5.Mode=Slave_8_bits_External_Synchro
PE5.Signal=DCMI_D6

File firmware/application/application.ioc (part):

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Mcu.Name=STM32F446V(C-E)Tx
Mcu.Package=LQFP100
Mcu.UserName=STM32F446VETx
PA0-WKUP.GPIOParameters=GPIO_Label,GPIO_ModeDefaultEXTI
PA0-WKUP.GPIO_Label=WKUP
PA0-WKUP.GPIO_ModeDefaultEXTI=GPIO_MODE_IT_FALLING
PA0-WKUP.Signal=GPXTI0
PA13.Mode=Trace_Asynchronous_SW
PA13.Signal=SYS_JTMS-SWDIO
PA14.Mode=Trace_Asynchronous_SW
PA14.Signal=SYS_JTCK-SWCLK
PA4.Mode=Slave_8_bits_External_Synchro
PA4.Signal=DCMI_HSYNC
PA6.Mode=Slave_8_bits_External_Synchro
PA6.Signal=DCMI_PIXCLK
PA8.Mode=Clock-out-1
PA8.Signal=RCC_MCO_1
PB3.Mode=Trace_Asynchronous_SW
PB3.Signal=SYS_JTDO-SWO
PB6.GPIOParameters=GPIO_Label,GPIO_Pu
PB6.GPIO_Label=Cam_SCL
PB6.GPIO_Pu=GPIO_NOPULL
PB6.Mode=I2C
PB6.Signal=I2C1_SCL
PB7.Mode=Slave_8_bits_External_Synchro
PB7.Signal=DCMI_VSYNC
PB9.GPIOParameters=GPIO_Label,GPIO_Pu,GPIO_Mode
PB9.GPIO_Label=Cam_SDA
PB9.GPIO_Mode=GPIO_MODE_AF_OD
PB9.GPIO_Pu=GPIO_NOPULL
PB9.Mode=I2C
PB9.Signal=I2C1_SDA
PC10.Mode=SD_4_bits_Wide_bus
PC10.Signal=SDIO_D2
PC11.Mode=SD_4_bits_Wide_bus
PC11.Signal=SDIO_D3
PC12.Mode=SD_4_bits_Wide_bus
PC12.Signal=SDIO_CK
PC13.Mode=SYS_WakeUp1
PC13.Signal=SYS_WKUP1
PC14-OSC32_IN.Mode=LSE-External-Oscillator
PC14-OSC32_IN.Signal=RCC_OSC32_IN
PC15-OSC32_OUT.Mode=LSE-External-Oscillator
PC15-OSC32_OUT.Signal=RCC_OSC32_OUT
PC6.Mode=Slave_8_bits_External_Synchro
PC6.Signal=DCMI_D0
PC7.Mode=Slave_8_bits_External_Synchro
PC7.Signal=DCMI_D1
PC8.Mode=SD_4_bits_Wide_bus
PC8.Signal=SDIO_D0
PC9.Mode=SD_4_bits_Wide_bus
PC9.Signal=SDIO_D1
PD1.GPIOParameters=GPIO_Label
PD1.GPIO_Label=SD_DETECT
PD1.Signal=GPIO_Input
PD15.GPIOParameters=GPIO_PuPd,GPIO_Label
PD15.GPIO_Label=CAM_ENABLE
PD15.GPIO_PuPd=GPIO_NOPULL
PD15.Signal=GPIO_Output
PD2.Mode=SD_4_bits_Wide_bus
PD2.Signal=SDIO_CMD
PD3.Mode=Slave_8_bits_External_Synchro
PD3.Signal=DCMI_D5
PD7.GPIOParameters=GPIO_Speed,GPIO_Label
PD7.GPIO_Label=CAM_PWDN
PD7.GPIO_Speed=GPIO_SPEED_FREQ_LOW
PD7.Signal=GPIO_Output
PE0.Mode=Slave_8_bits_External_Synchro
PE0.Signal=DCMI_D2
PE1.Mode=Slave_8_bits_External_Synchro
PE1.Signal=DCMI_D3
PE14.GPIOParameters=GPIO_Label
PE14.GPIO_Label=STAT
PE14.Signal=GPIO_Output
PE4.Mode=Slave_8_bits_External_Synchro
PE4.Signal=DCMI_D4
PE5.Mode=Slave_8_bits_External_Synchro
PE5.Signal=DCMI_D6
PE6.Mode=Slave_8_bits_External_Synchro
PE6.Signal=DCMI_D7
PH0-OSC_IN.Mode=HSE-External-Oscillator
PH0-OSC_IN.Signal=RCC_OSC_IN
PH1-OSC_OUT.Mode=HSE-External-Oscillator
PH1-OSC_OUT.Signal=RCC_OSC_OUT
RCC.HSE_VALUE=24000000
RCC.SYSCLKFreq_VALUE=180000000
RCC.SYSCLKSource=RCC_SYSCLKSOURCE_PLLCLK
board=custom

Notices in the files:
hardware/electrical/3885.kicad_pcb:
© Frank Plowman 2023
